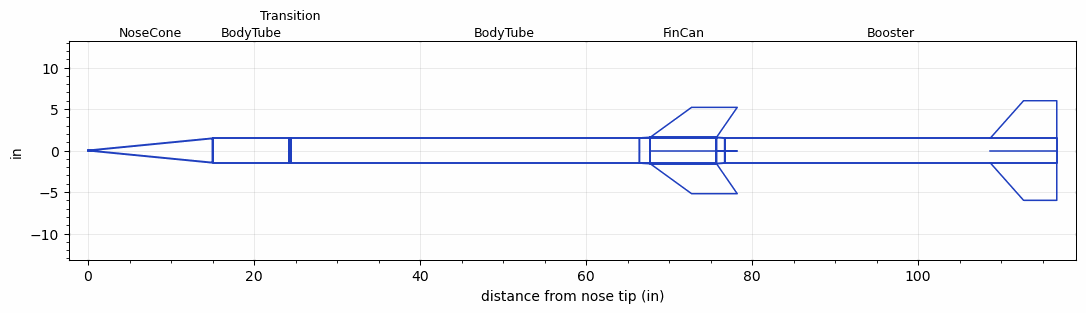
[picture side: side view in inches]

<RASAeroDocument>
 <FileVersion>2</FileVersion>
 <RocketDesign>
  <NoseCone>
   <Length>15</Length>
   <Diameter>2.93</Diameter>
   <Shape>Conical</Shape>
   <BluntRadius>0.1</BluntRadius>
   <Location>0</Location>
  </NoseCone>
  <BodyTube>
   <Length>9.214</Length>
   <Diameter>2.93</Diameter>
   <Location>15</Location>
  </BodyTube>
  <Transition>
   <Length>0.25</Length>
   <Diameter>3</Diameter>
   <Location>24.214</Location>
   <RearDiameter>3</RearDiameter>
  </Transition>
  <BodyTube>
   <Length>51.25</Length>
   <Diameter>3</Diameter>
   <Location>24.464</Location>
  </BodyTube>
  <FinCan>
   <Length>8</Length>
   <Diameter>3.15</Diameter>
   <InsideDiameter>3</InsideDiameter>
   <Location>75.714</Location>
   <ShoulderLength>1.288</ShoulderLength>
   <Offset>-8</Offset>
   <Fin>
    <Count>4</Count>
    <Chord>8</Chord>
    <Span>3.625</Span>
    <SweepDistance>5</SweepDistance>
    <TipChord>5.5</TipChord>
    <Thickness>0.157</Thickness>
    <Location>8</Location>
    <AirfoilSection>Hexagonal</AirfoilSection>
    <FX1>0.75</FX1>
    <FX3>0.75</FX3>
   </Fin>
  </FinCan>
  <Booster>
   <Length>40</Length>
   <Diameter>3</Diameter>
   <InsideDiameter>3.15</InsideDiameter>
   <Location>75.714</Location>
   <ShoulderLength>1</ShoulderLength>
   <Fin>
    <Count>4</Count>
    <Chord>8</Chord>
    <Span>4.5</Span>
    <SweepDistance>4</SweepDistance>
    <TipChord>4</TipChord>
    <Thickness>0.118</Thickness>
    <Location>8</Location>
    <AirfoilSection>Hexagonal</AirfoilSection>
    <FX1>1</FX1>
    <FX3>0.75</FX3>
   </Fin>
  </Booster>
  <Surface>Rough Camouflage Paint</Surface>
  <ModifiedBarrowman>True</ModifiedBarrowman>
  <Turbulence>True</Turbulence>
  <UseBooster1>True</UseBooster1>
  <UseBooster2>False</UseBooster2>
 </RocketDesign>
 <LaunchSite>
  <Altitude>2000</Altitude>
  <Pressure>29.92</Pressure>
  <RodAngle>0</RodAngle>
  <RodLength>15</RodLength>
  <Temperature>51.868</Temperature>
  <WindSpeed>0</WindSpeed>
 </LaunchSite>
 <Recovery>
  <Altitude1>2000</Altitude1>
  <Altitude2>2000</Altitude2>
  <DeviceType1>Parachute</DeviceType1>
  <DeviceType2>Parachute</DeviceType2>
  <Event1>True</Event1>
  <Event2>True</Event2>
  <Size1>8</Size1>
  <Size2>28</Size2>
  <EventType1>Apogee</EventType1>
  <EventType2>Altitude</EventType2>
  <CD1>0.8</CD1>
  <CD2>1.8</CD2>
 </Recovery>
 <SimulationList>
  <Simulation>
   <SustainerEngine>N3051  (TsKrush)</SustainerEngine>
   <SustainerLaunchWt>22.69</SustainerLaunchWt>
   <SustainerNozzleDiameter>2.5</SustainerNozzleDiameter>
   <SustainerCG>44.19</SustainerCG>
   <SustainerIgnitionDelay>10</SustainerIgnitionDelay>
   <Booster1Engine>M3140  (TsKrush)</Booster1Engine>
   <Booster1LaunchWt>38.82</Booster1LaunchWt>
   <Booster1SeparationDelay>0</Booster1SeparationDelay>
   <Booster1IgnitionDelay>0</Booster1IgnitionDelay>
   <Booster1CG>63.22</Booster1CG>
   <Booster1NozzleDiameter>2.75</Booster1NozzleDiameter>
   <IncludeBooster1>True</IncludeBooster1>
   <Booster2Delay>0</Booster2Delay>
   <IncludeBooster2>False</IncludeBooster2>
   <TimetoApogee>86.72958</TimetoApogee>
   <MaxAltitude>114538</MaxAltitude>
   <MaxVelocity>4451.844</MaxVelocity>
  </Simulation>
 </SimulationList>
</RASAeroDocument>
